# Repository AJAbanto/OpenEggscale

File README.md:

# OpenEggscale
 open source eggscale

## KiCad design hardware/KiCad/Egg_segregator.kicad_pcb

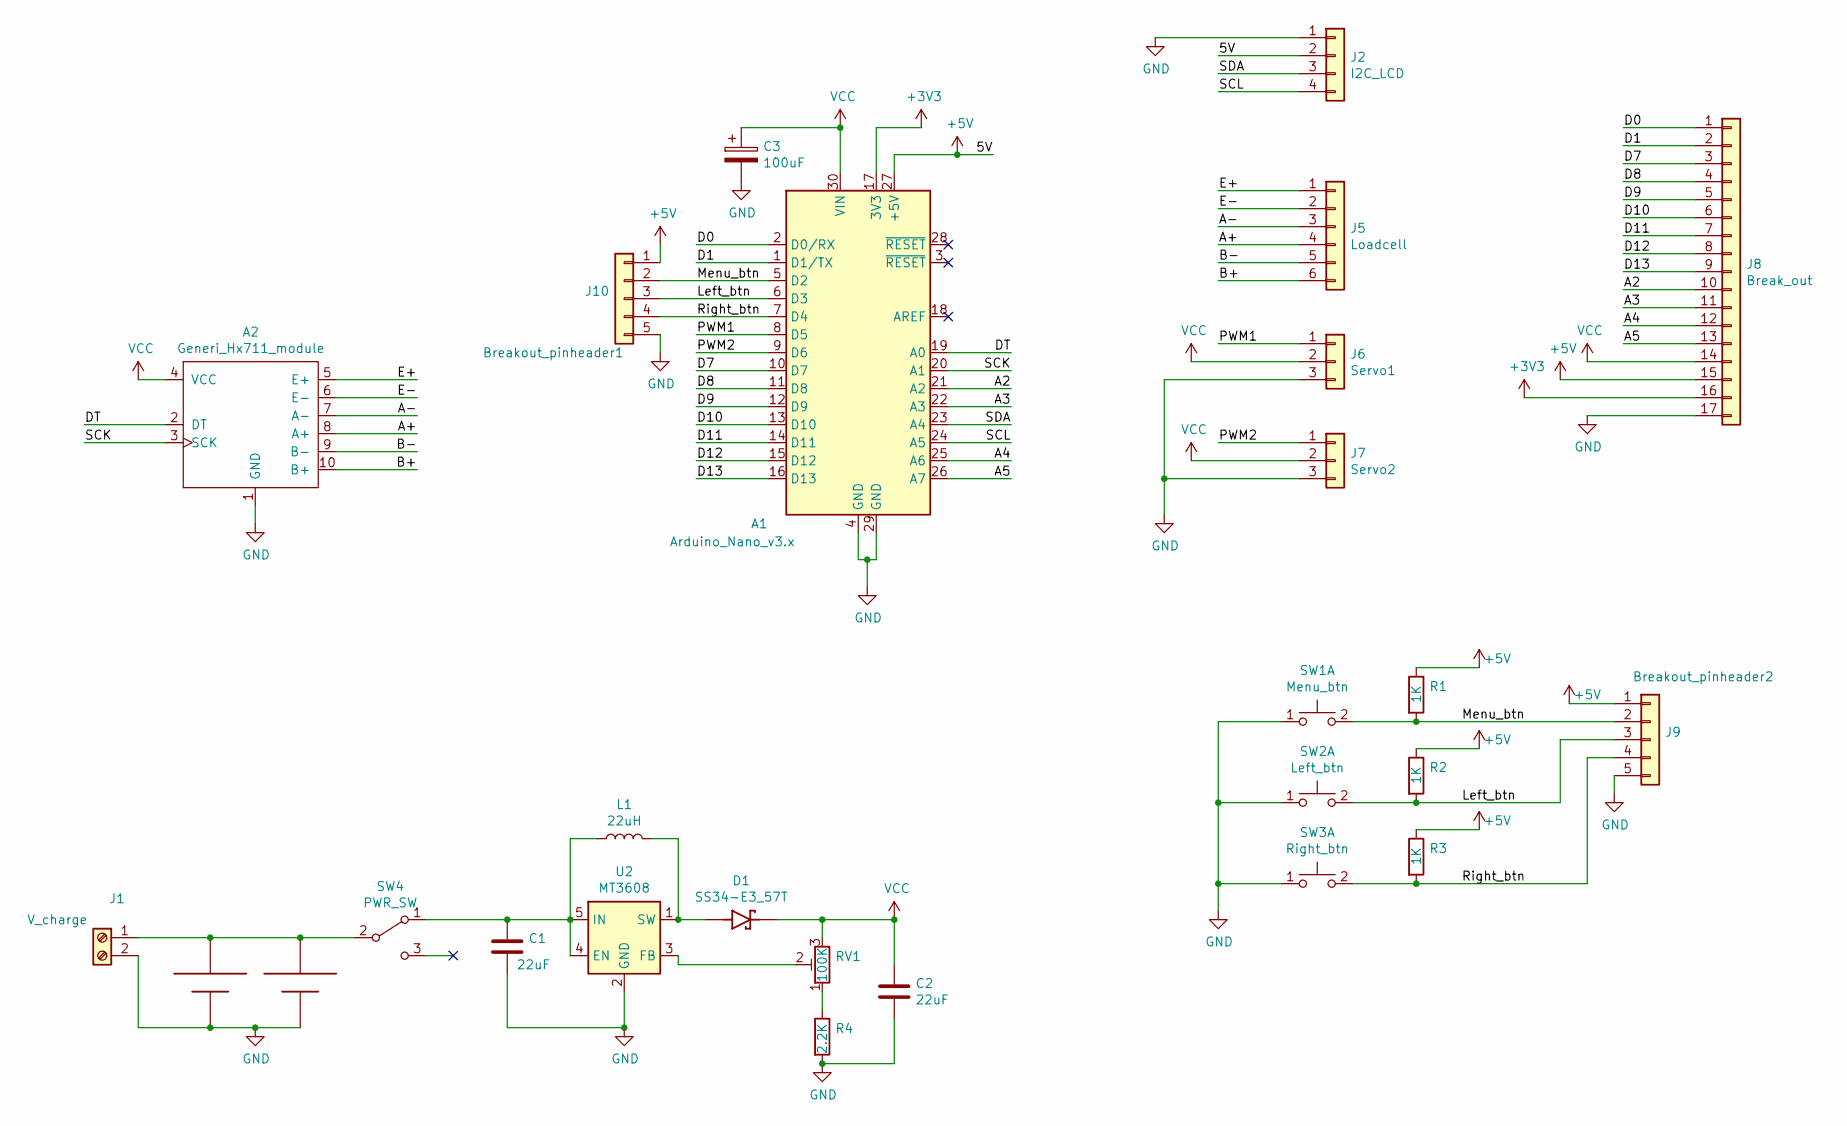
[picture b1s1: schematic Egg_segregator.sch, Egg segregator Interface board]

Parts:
A1: Arduino_Nano_v3.x; Arduino_Nano
A2: Generi_Hx711_module; Generic_Hx711_module
C1, C2: 22uF; C_0805_2012Metric_Pad1.15x1.40mm_HandSolder
C3: 100uF; CP_Radial_D8.0mm_P3.50mm
D1: SS34-E3_57T; DIOM7959X262N
J1: V_charge; TerminalBlock_bornier-2_P5.08mm
J2: I2C_LCD; PinSocket_1x04_P2.54mm_Vertical
J5: Loadcell; PinSocket_1x06_P2.54mm_Vertical
J6: Servo1; PinSocket_1x03_P2.54mm_Vertical
J7: Servo2; PinSocket_1x03_P2.54mm_Vertical
J8: Break_out; PinSocket_1x17_P2.54mm_Vertical
J9: Breakout_pinheader2; PinSocket_1x05_P2.54mm_Vertical
J10: Breakout_pinheader1; PinSocket_1x05_P2.54mm_Vertical
L1: 22uH; L_10.4x10.4_H4.8
R1, R2, R3: 1K; R_0603_1608Metric_Pad1.05x0.95mm_HandSolder
R4: 2.2K; R_0603_1608Metric_Pad1.05x0.95mm_HandSolder
RV1: 100K; Potentiometer_Bourns_3266W_Vertical
SW1: Menu_btn; SW_PUSH_6mm
SW2: Left_btn; SW_PUSH_6mm
SW3: Right_btn; SW_PUSH_6mm
SW4: PWR_SW; PinHeader_1x03_P2.54mm_Vertical
U1: BK-18650-PC4; 18650-PC4
U2: MT3608; SOT-23-6

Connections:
+3V3: A1.17 (3V3), J8.16
+5V: A1.27 (+5V), J2.2, J8.15, J9.1, J10.1, R1.1, R2.1, R3.1
/A2: A1.21 (A2), J8.10
/A3: A1.22 (A3), J8.11
/A4: A1.25 (A6), J8.12
/A5: A1.26 (A7), J8.13
/A+: A2.8 (A+), J5.4
/A-: A2.7 (A-), J5.3
/B+: A2.10 (B+), J5.6
/B-: A2.9 (B-), J5.5
/D0: A1.2 (D0/RX), J8.1
/D1: A1.1 (D1/TX), J8.2
/D7: A1.10 (D7), J8.3
/D8: A1.11 (D8), J8.4
/D9: A1.12 (D9), J8.5
/D10: A1.13 (D10), J8.6
/D11: A1.14 (D11), J8.7
/D12: A1.15 (D12), J8.8
/D13: A1.16 (D13), J8.9
/DT: A1.19 (A0), A2.2 (DT)
/E+: A2.5 (E+), J5.1
/E-: A2.6 (E-), J5.2
/Left_btn: A1.6 (D3), J9.3, J10.3, R2.2, SW2.2 (D)
/Menu_btn: A1.5 (D2), J9.2, J10.2, R1.2, SW1.2 (D)
/PWM1: A1.8 (D5), J6.1
/PWM2: A1.9 (D6), J7.1
/Right_btn: A1.7 (D4), J9.4, J10.4, R3.2, SW3.2 (D)
/SCK: A1.20 (A1), A2.3 (SCK)
/SCL: A1.24 (A5), J2.4
/SDA: A1.23 (A4), J2.3
GND: A1.4 (GND), A1.29 (GND), A2.1 (GND), C1.2, C2.2, C3.2, J1.2, J2.1, J6.3, J7.3, J8.17, J9.5, J10.5, R4.2, SW1.1 (C), SW2.1 (C), SW3.1 (C), U1.1 (-1), U1.2 (-2), U2.2 (GND)
unnamed: C1.1, L1.1, SW4.1 (A), U2.4 (EN), U2.5 (IN)
unnamed: D1.A, L1.2, U2.1 (SW)
unnamed: J1.1, SW4.2 (B), U1.+1, U1.+2
unnamed: R4.1, RV1.1
unnamed: RV1.2, U2.3 (FB)
VCC: A1.30 (VIN), A2.4 (VCC), C2.1, C3.1, D1.C, J6.2, J7.2, J8.14, RV1.3

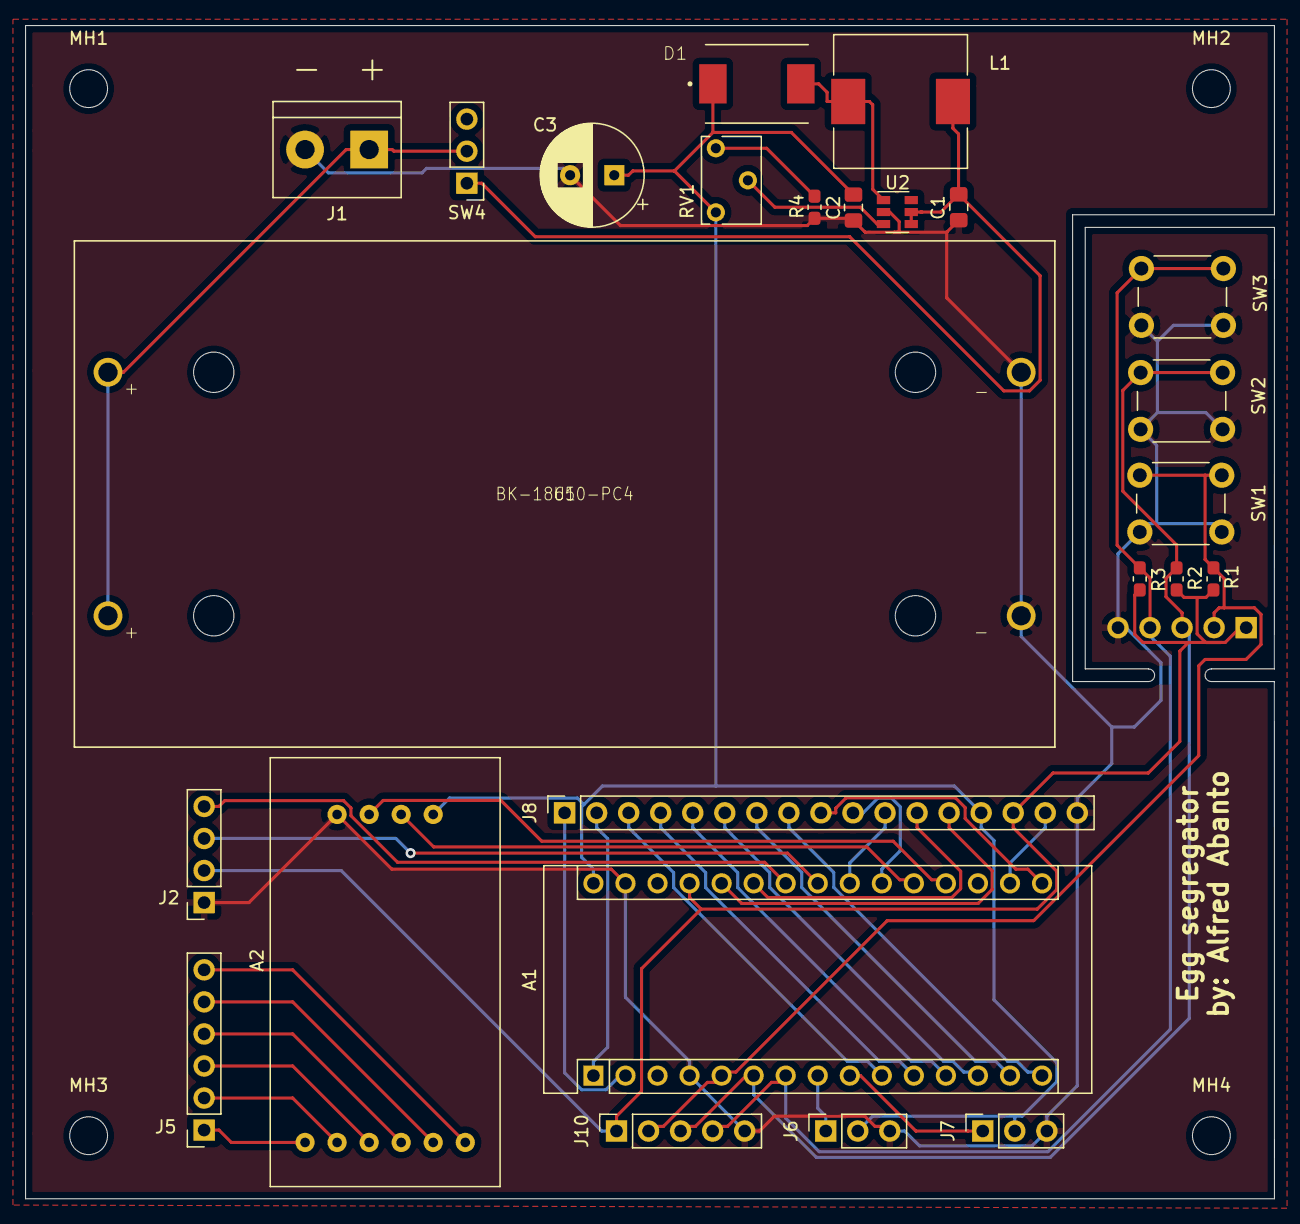
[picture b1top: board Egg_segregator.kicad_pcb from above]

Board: 2 copper layers, 99.0 x 93.0 mm, 30 parts (1 on the bottom side), 37 nets.

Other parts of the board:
MH1, MH2, MH3, MH4: MountingHole_3mm

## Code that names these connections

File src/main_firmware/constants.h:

LiquidCrystal_I2C lcd(0x27,20,4);  // set the LCD address to 0x27 for a 16 chars and 2 line display

HX711 scale;


/* -------------Pin assignments------------
 * ----HX711----
 * A0 - Dt pin
 * A1 - SCK pin
 * 
 * ---I2C LCD---
 * A4 - SDA
 * A5 - SCL
 * 
 */


/*
//Old weight tresholds from 24/08/2020

//Jumbo 81.0 onwards
#define JUMBO_MIN 81.0

//2X 80.0-74.0
#define XXL_MAX 79.0
#define XXL_MIN 74.0

//XL 69.0-64.6
#define XL_MAX 69.0
#define XL_MIN 64.6

//L 64.5-58.0
#define L_MAX 64.5
#define L_MIN 58.0

//M 57.8-54.5
#define M_MAX 57.8
#define M_MIN 54.5

//S 54.0-49.0
#define S_MAX 54.0
#define S_MIN 49.0

//XS 48.0-10.0
#define XS_MAX 48.0
#define XS_MIN 10.0
*/



//Finite state machine states
#define MAIN_STATE 0
#define MENU_STATE 1
#define CONFIG_STATE 2
#define CONFIG_CHANGE_MIN 3
#define CONFIG_CHANGE_MAX 4
#define CALLIBRATE_STATE 5


//Btn pins
#define MENU_BTN_PIN 2
#define LEFT_BTN_PIN 3
#define RIGHT_BTN_PIN 4

//Btn debounce time (in ms)
#define DEBOUNCE_DELAY 50

//State transition delay (in ms)
#define TRANSITION_DELAY 500
//Menu options
#define TARE_OPTN 0
#define CONFIG_OPTN 1
#define CALLIBRATE_OPTN 2
#define EXT_OPTN 3


//Config options
#define XS_OPTN 0
#define S_OPTN 1
#define M_OPTN 2
#define L_OPTN 3
#define XL_OPTN 4
#define XXL_OPTN 5
#define JB_OPTN 6
#define CEXT_OPTN 7




float JUMBO_MIN = 79.0;

//2X 80.0-74.0
float XXL_MAX = 77.0;
float XXL_MIN = 72.0;

//XL 69.0-64.6
float XL_MAX = 67.0;
float XL_MIN = 62.6;

//L 64.5-58.0
float L_MAX = 62.5;
float L_MIN = 56.0;

//M 57.8-54.5
float M_MAX = 55.8;
float M_MIN = 52.5;

//S 54.0-49.0
float S_MAX = 52.0;
float S_MIN = 47.0;

//XS 48.0-10.0
float XS_MAX = 46.0;
float XS_MIN = 8.0;

//callibration factor
float callibration_factor = 615.31;

//state transition variables
int c_state , n_state;

//flag
boolean menu_press, left_press, right_press;

//for debouncing
int left_btn_state, last_left_btn_state;
int right_btn_state, last_right_btn_state;
int menu_btn_state, last_menu_btn_state;

//for menu/config options
int optn;

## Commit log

2020-08-12 Initial upload of files
    Initial upload of files
2020-08-13 offset current threshold and uploaded into eeprom
    updated current threshold for first round of testing.
2020-08-23 software updates and file organization
    Added some software updates and pcb changes
